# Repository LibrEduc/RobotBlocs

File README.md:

RobotBlocs
===================
tangible programmation of drawing robot, by kids for kids.

[Click here to launch video: https://mediacad.ac-nantes.fr/m/2332](https://mediacad.ac-nantes.fr/m/2332)

**==>**[**Animation à ouvrir.**](https://github.com/technologiescollege/RobotBlocs/blob/master/principe.swf?raw=true)

Designers & developpers
----------
Chaque version du projet, chaque année, chaque groupe et chaque organisation a été différente.
Vous trouverez les noms des élèves, quand ils ont bien voulu qu'on les laisse, dans les dossiers (électronique ou Modeles_3D\Solidworks) de chaque année.

Each version of the project, each year, each group and each organisation has been different.
You will find the names of the students, when they were willing to be left, in the folders (electronic or Modeles_3D\Solidworks) of each year.

Explanation/explication
----------

Les enfants jouent naturellement avec leurs mains et apprennent avec dès leurs premières années, construisant toute sorte de choses qui peuvent les amuser mais aussi en faisant ces choses ensemble. Un des avantages de la programmation tangible est qu'il rend l'idée du programme physique, afin que les enfants puissent jouer avec, le manipuler et refaire autant que voulu avant de le téléverser. La tranche d'âge visée est celle d'enfants entre 6 et 7 ans. 

Notre problématique est la suivante : "concevoir un système permettant à des enfants âgés de 6 ans ou plus, sachant lire ou pas, avec des difficultés motrices ou pas, d'apprendre les bases de la programmation et de l’algorithmique". 

A la suite de la lecture du cahier des charges fonctionnels, nous pouvons donc affirmer que nous devons concevoir un système composé de 3 sous-systèmes : 

 - un bloc maître qui transmet les informations des blocs programmes à un robot dessinateur.  
 - des blocs programmes qui auront une fonction, liée aux mouvements du robot,définie par un couvercle amovible ainsi qu'une capacité à s'emboîter entre eux afin de former une chaîne pour transmettre l'information. 
 - un robot dessinateur motorisé autonome en énergie qui possédera une partie mobile pour déplacer un crayon, d'un diamètre de 8mm à 15mm, afin de tracer des formes sur papier. Il exécutera les commandes des blocs programmes envoyées via le bloc maître.

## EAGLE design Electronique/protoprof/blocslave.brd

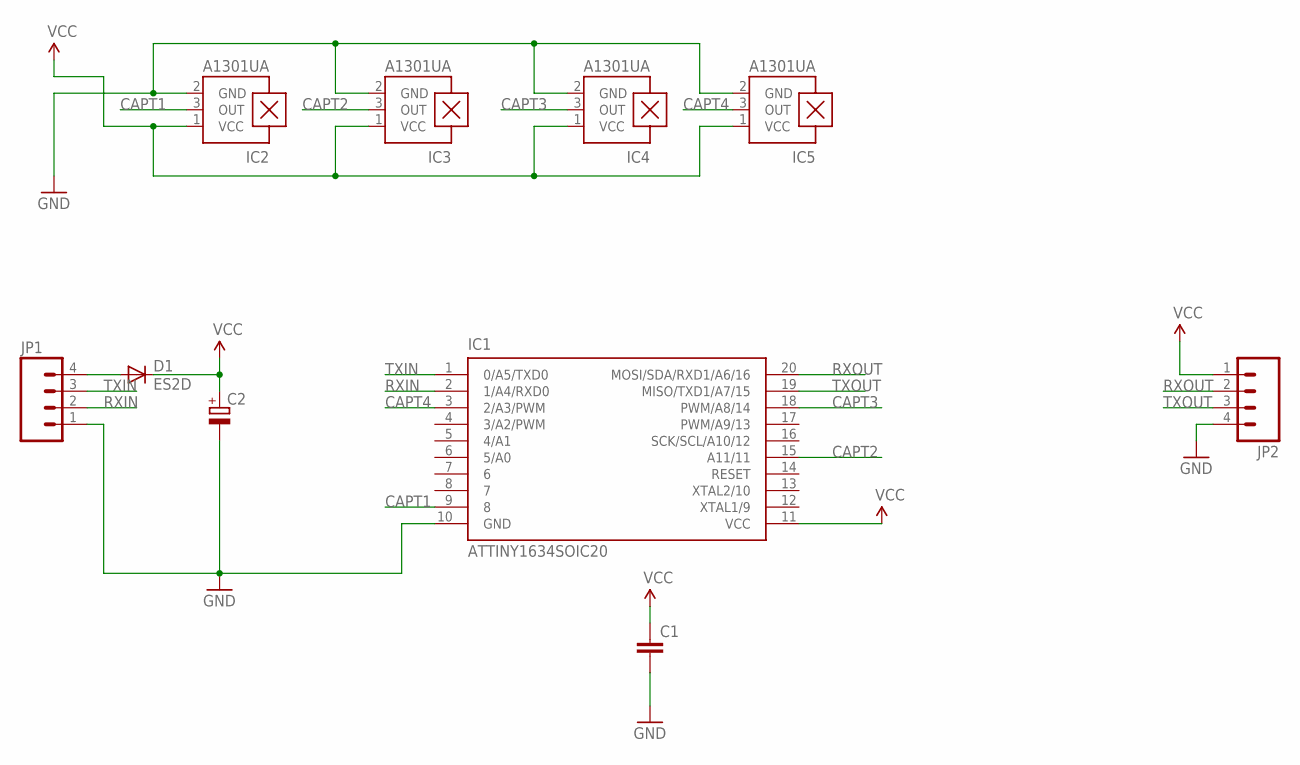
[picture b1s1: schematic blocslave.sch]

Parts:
C1: C-EUC1206; C1206
C2: CPOL-EUSMCD; SMC_D
D1: ES2D; SMB
IC1: ATTINY1634SOIC20; SOIC20
IC2, IC3, IC4, IC5: A1301UA; SIP3-UA
JP1, JP2: M04; 1X04

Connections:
CAPT1: IC1.9 (8), IC2.3 (OUT)
CAPT2: IC1.15 (A11/11), IC3.3 (OUT)
CAPT3: IC1.18 (PWM/A8/14), IC4.3 (OUT)
CAPT4: IC1.3 (2/A3/PWM), IC5.3 (OUT)
GND: C1.2, C2.-, IC1.10 (GND), IC2.2 (GND), IC3.2 (GND), IC4.2 (GND), IC5.2 (GND), JP1.1, JP2.4
unnamed: D1.A, JP1.4
RXIN: IC1.2 (1/A4/RXD0), JP1.2
RXOUT: IC1.20 (MOSI/SDA/RXD1/A6/16), JP2.2
TXIN: IC1.1 (0/A5/TXD0), JP1.3
TXOUT: IC1.19 (MISO/TXD1/A7/15), JP2.3
VCC: C1.1, C2.+, D1.C, IC1.11 (VCC), IC2.1 (VCC), IC3.1 (VCC), IC4.1 (VCC), IC5.1 (VCC), JP2.1

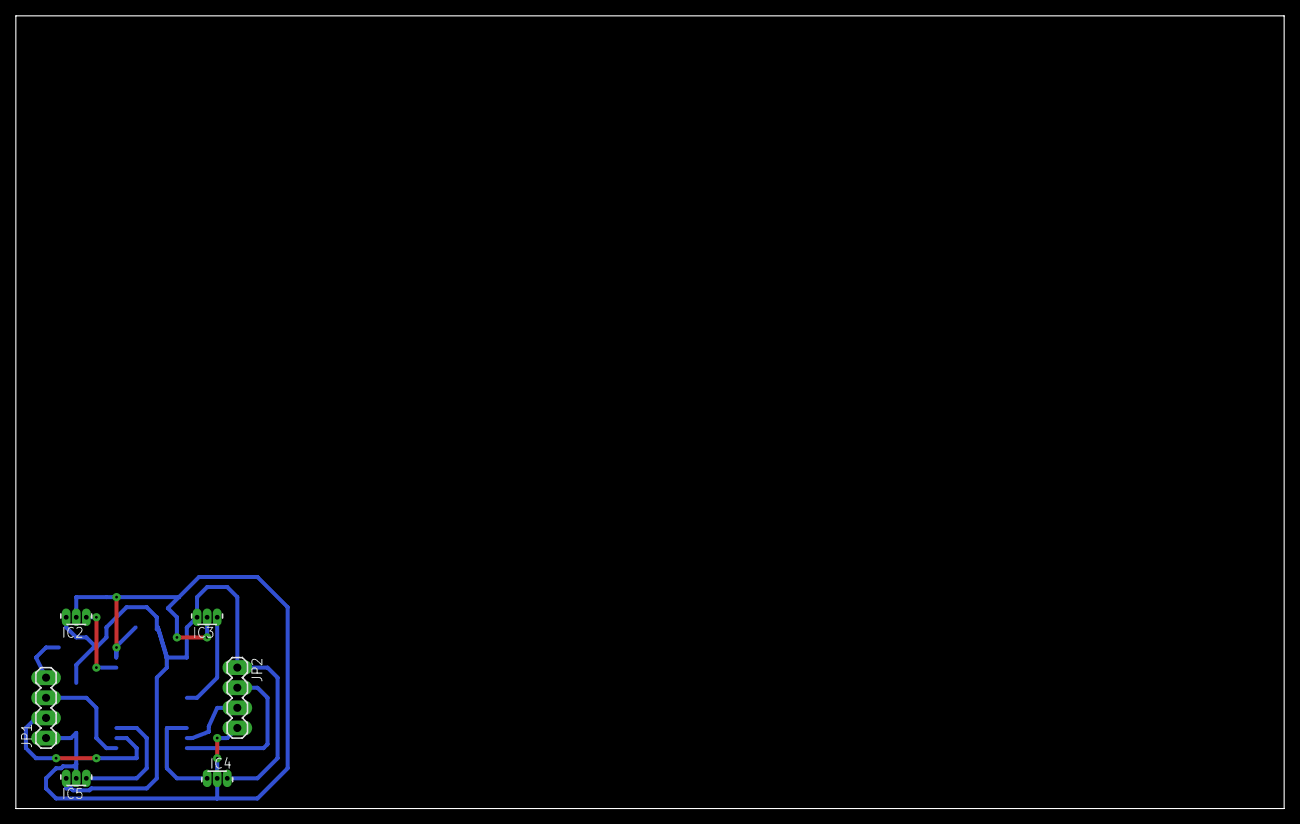
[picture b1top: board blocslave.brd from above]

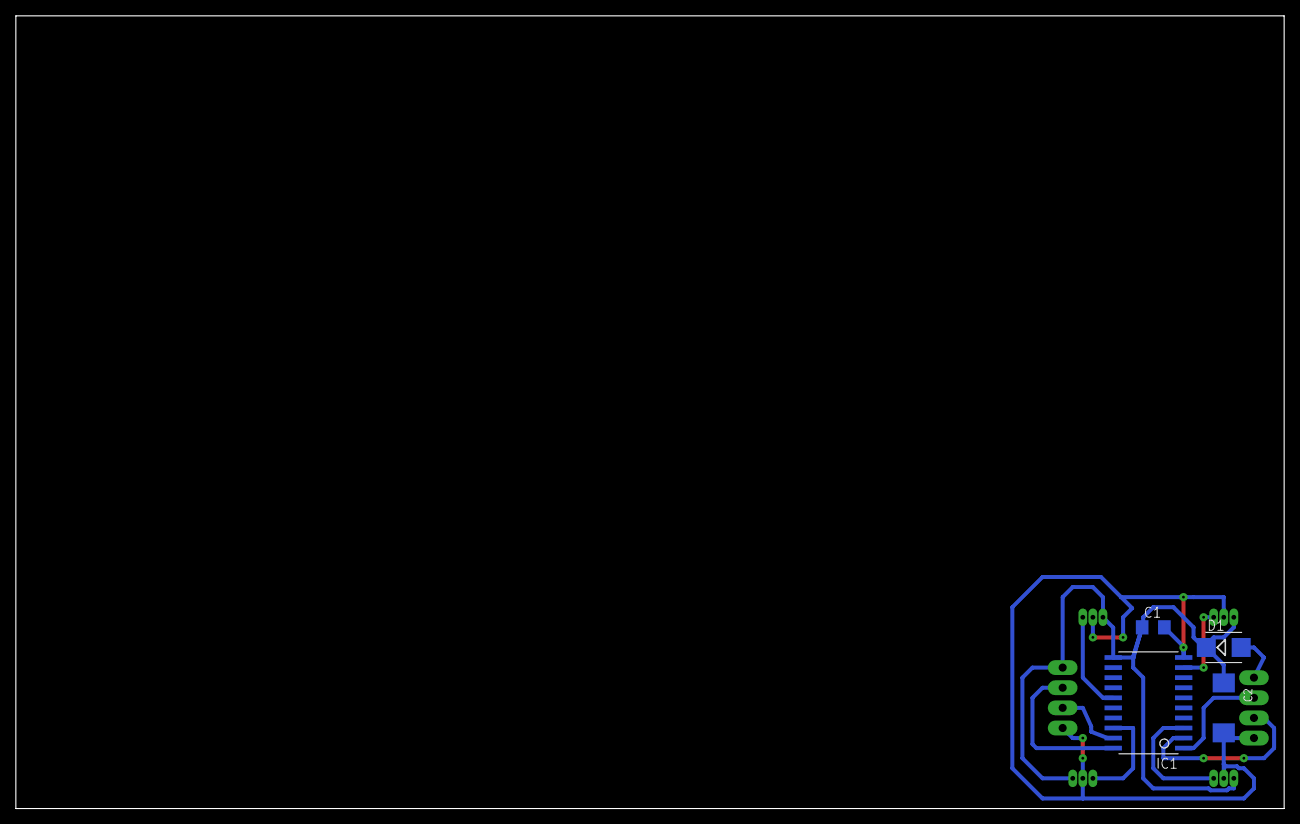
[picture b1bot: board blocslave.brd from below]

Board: 2 copper layers, 160.0 x 100.0 mm, 10 parts (4 on the bottom side), 11 nets.

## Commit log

2017-06-28 first upload
2017-06-28 documents
2017-06-28 upload arduino programs
2017-06-28 3D models
2017-06-28 solidworks models
2017-06-28 videos
2020-07-11 Cleaning
2020-07-11 add new files
2021-02-01 nettoyage + rajout versions
2021-02-01 cleaning + adding slideshow
2021-07-25 add v2020-2021
2021-09-23 add Robot

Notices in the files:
parts and their libraries:
SparkFun-Aesthetics: Licensing: Creative Commons ShareAlike 4.0 International - https://creativecommons.org/licenses/by-sa/4.0
